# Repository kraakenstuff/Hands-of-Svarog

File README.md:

# Hands of Svarog
 A 6HP Eurorack panning mixer and phones output. 
 
 It is inspired by Synthrotek's MST Stereo Output Mixer (https://store.synthrotek.com/MST_Stereo_Output_Mixer). The schematic is based on J3RK's schematic found here: https://www.muffwiggler.com/forum/viewtopic.php?t=224595. I've included a couple of inputs more, swapped his OPA2604 for NJM2068 (because that's what I had) and changed his 33k resistors in output stage for 12k (experiment with those resistors and find a pair that suits your headphones).
 
 As for the functionality, you set levels for your 4 inputs. Then you can pan group A (inputs 1 and 2) and group B (inputs 3 and 4)
 
Note: I wanted panel for this module to include a mixture of Slavic mythology and heavy metal (yeah, why not). But after I made the panel, friends suggested that some symbols ("kolovrat" - a wheel looking one) look like nazi symbols, so I made the (official) panel that is clean and acceptable for all (panel1.png). However, I included the original design here as well (panel.png), without making panel files (in case you find it cool, non-offensive and you make panels for yourself).

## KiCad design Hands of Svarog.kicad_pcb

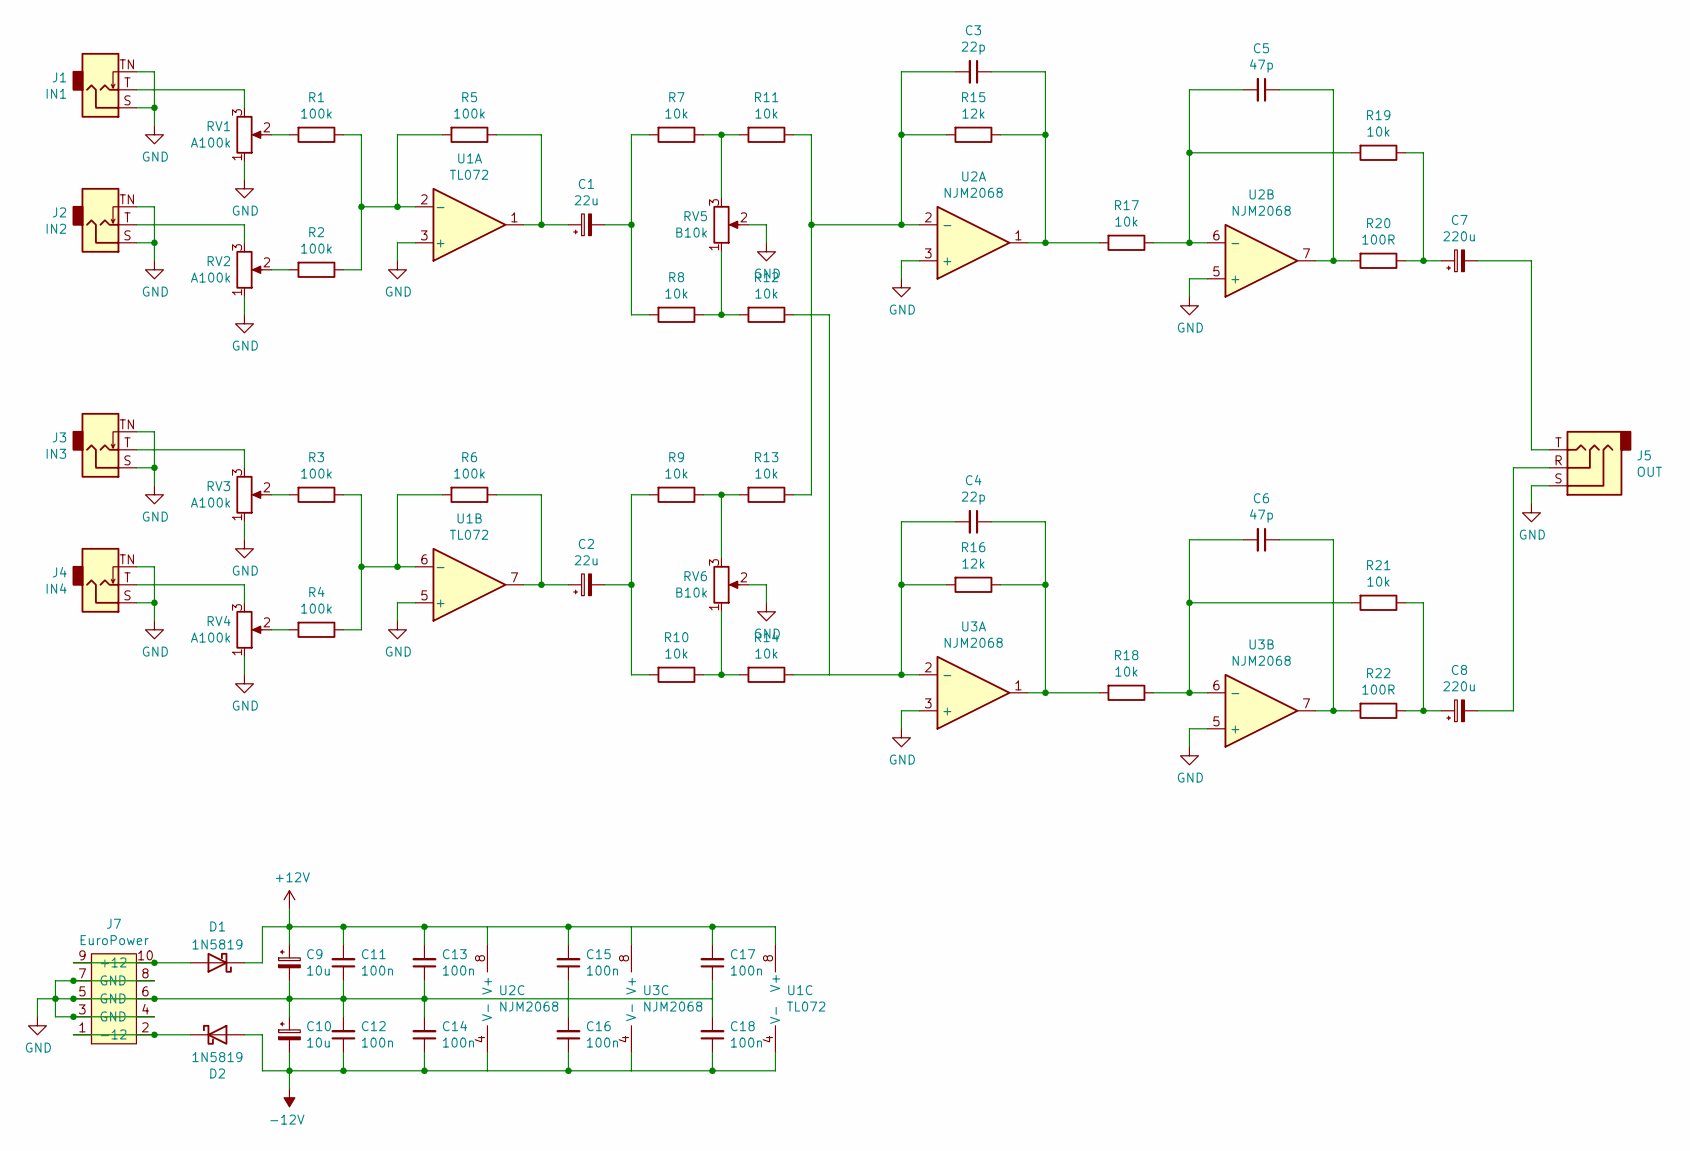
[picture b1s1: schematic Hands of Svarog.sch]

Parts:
C1, C2: 22u; CP_Elec_5x5.9
C3, C4: 22p; C_0603_1608Metric_Pad1.05x0.95mm_HandSolder
C5, C6: 47p; C_0603_1608Metric_Pad1.05x0.95mm_HandSolder
C7, C8: 220u; CP_Elec_8x10
C9, C10: 10u; CP_Elec_5x5.9
C11, C12, C13, C14, C15, C16, C17, C18: 100n; C_0603_1608Metric_Pad1.05x0.95mm_HandSolder
D1, D2: 1N5819; D_SOD-123
J1: IN1; PJ301M-12-NoHole
J2: IN2; PJ301M-12-NoHole
J3: IN3; PJ301M-12-NoHole
J4: IN4; PJ301M-12-NoHole
J5: OUT; PJ366ST
J7: EuroPower; EuroHeader10
R1, R2, R3, R4, R5, R6: 100k; R_0603_1608Metric_Pad0.98x0.95mm_HandSolder
R7, R8, R9, R10, R11, R12, R13, R14, R17, R18, R19, R21: 10k; R_0603_1608Metric_Pad0.98x0.95mm_HandSolder
R15, R16: 12k; R_0603_1608Metric_Pad0.98x0.95mm_HandSolder
R20, R22: 100R; R_0603_1608Metric_Pad0.98x0.95mm_HandSolder
RV1, RV2, RV3, RV4: A100k; POT-9MM-ALPHA
RV5, RV6: B10k; POT-9MM-ALPHA
U1: TL072; SOIC-8_5.23x5.23mm_P1.27mm
U2, U3: NJM2068; SOIC-8_5.23x5.23mm_P1.27mm

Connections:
+12V: C9.1, C11.2, C13.2, C15.2, C17.2, D1.1 (K), U1.8 (V+), U2.8 (V+), U3.8 (V+)
-12V: C10.2, C12.1, C14.1, C16.1, C18.1, D2.2 (A), U1.4 (V-), U2.4 (V-), U3.4 (V-)
GND: C9.2, C10.1, C11.1, C12.2, C13.1, C14.2, C15.1, C16.2, C17.1, C18.2, J1.S, J1.TN, J2.S, J2.TN, J3.S, J3.TN, J4.S, J4.TN, J5.S, J7.3 (GND), J7.4, J7.5 (GND), J7.6, J7.7 (GND), J7.8, RV1.1, RV2.1, RV3.1, RV4.1, RV5.2, RV6.2, U1.3 (+), U1.5 (+), U2.3 (+), U2.5 (+), U3.3 (+), U3.5 (+)
unnamed: C1.1, R5.1, U1.1
unnamed: C1.2, R7.2, R8.2
unnamed: C2.1, R6.1, U1.7
unnamed: C2.2, R9.2, R10.2
unnamed: C3.1, R15.1, R17.2, U2.1
unnamed: C3.2, R11.1, R13.1, R15.2, U2.2 (-)
unnamed: C4.1, R16.1, R18.2, U3.1
unnamed: C4.2, R12.1, R14.1, R16.2, U3.2 (-)
unnamed: C5.1, R20.2, U2.7
unnamed: C5.2, R17.1, R19.2, U2.6 (-)
unnamed: C6.1, R22.2, U3.7
unnamed: C6.2, R18.1, R21.2, U3.6 (-)
unnamed: C7.1, R19.1, R20.1
unnamed: C7.2, J5.T
unnamed: C8.1, R21.1, R22.1
unnamed: C8.2, J5.R
unnamed: D1.2 (A), J7.9 (+12), J7.10
unnamed: D2.1 (K), J7.1 (-12), J7.2
unnamed: J1.T, RV1.3
unnamed: J2.T, RV2.3
unnamed: J3.T, RV3.3
unnamed: J4.T, RV4.3
unnamed: R1.1, R2.1, R5.2, U1.2 (-)
unnamed: R1.2, RV1.2
unnamed: R2.2, RV2.2
unnamed: R3.1, R4.1, R6.2, U1.6 (-)
unnamed: R3.2, RV3.2
unnamed: R4.2, RV4.2
unnamed: R10.1, R14.2, RV6.1
unnamed: R7.1, R11.2, RV5.3
unnamed: R8.1, R12.2, RV5.1
unnamed: R9.1, R13.2, RV6.3

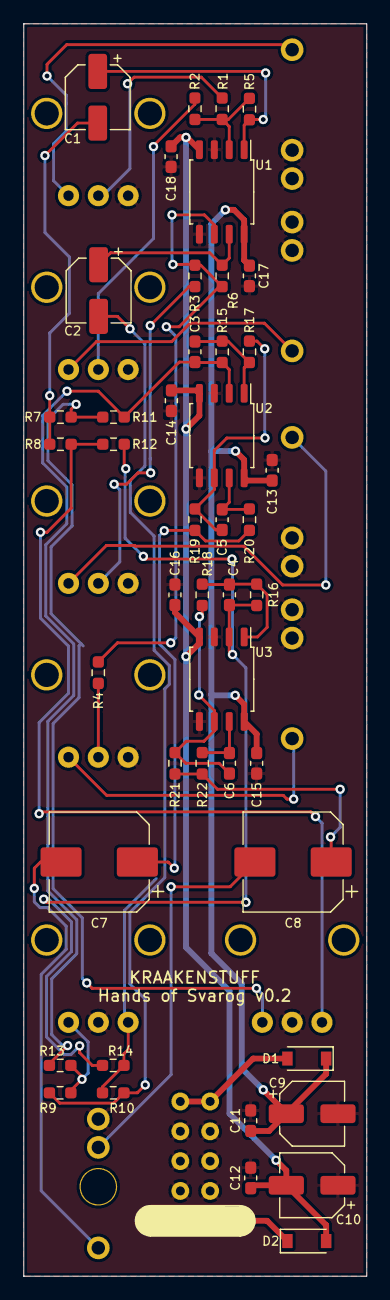
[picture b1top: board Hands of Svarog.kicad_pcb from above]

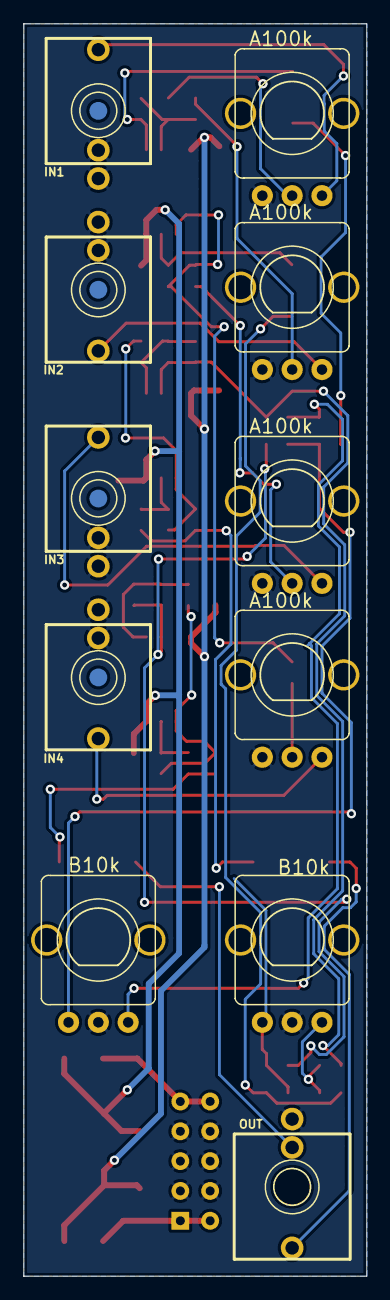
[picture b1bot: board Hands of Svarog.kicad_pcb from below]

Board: 2 copper layers, 29.2 x 106.7 mm, 57 parts (11 on the bottom side), 35 nets.

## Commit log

2021-03-02 Added v0.2 files
2021-03-03 Added gerber files
2021-03-17 Added panel design
2021-03-29 Fixed panel layout around panning knobs
2021-03-29 Updated panel gerbers
2021-04-04 Added a pic of the finished module
